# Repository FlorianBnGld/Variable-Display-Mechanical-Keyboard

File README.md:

### Florian Bonnet--Galand - ENSEA - 2025

# Le Clavier Reconfigurable

Ce projet s'inscrit dans l'option Maker de deuxième année à l'ENSEA. Il a été réalisé par Florian Bonnet--Galand.

---

#### Petite présentation vidéo du projet :

---

#### Le PCB

La première étape fut le design d'une PCB, intégrant les switchs Cherry MX RED, une STM32G474RET6, 4 multiplexeurs I2C TCA9548A, ainsi que des connecteurs 4 pins pour les écrans MCOT064032A1V-YI. Toutes les documentations et les fichiers du PCB sont à retrouver sur le GitHub du projet, juste en dessous. (Bon, vous êtes déjà dessus normalement mais bon...)

👉 [**Le GitHub du Projet**](https://github.com/FlorianBnGld/Variable-Display-Mechanical-Keyboard.git)

|  |  |
|:---:|:---:|

Ce premier design a été fait pour accueillir 30 touches, toutes similaires pour plus de modularité et accessoirement pour gagner du temps.

|  |
|:---:|

---

#### Les Keycaps

Un autre axe de travail sur lequel il a fallu plancher est celui des Keycaps.  
Il ne suffisait pas d'en trouver des correspondants sur Internet, mais bien de les faire sur mesure afin de les adapter aux écrans et aux switchs.  
Ils ont été imprimés en PLA sur des imprimantes Bambu Lab.

|  |  |
|:---:|:---:|

|  |  |
|:---:|:---:|

Ces Keycaps présentent un espace libre pour y placer l'écran, ainsi qu'une ouverture vers le dessous pour faire passer la nappe de connexion.

Au final, le modèle est assez satisfaisant :  
Ils s'adaptent parfaitement, aussi bien à la taille des écrans qui passent bien et surtout aux switchs.  
Les caps ne se retirent pas si facilement, bien que le modèle soit assez variable en fonction de la qualité d'impression.  
De plus, l'enlèvement du support était assez fastidieux et complexe sans endommager les keycaps.

|  | .jpg?raw=true) |
|:---:|:---:|

---

#### Ce qu'il reste à faire et potentielles améliorations futures

Afin de proposer un réel produit fini :
- Développer une interface utilisateur sur PC pour modifier ce que les touches tapent et ce qui s'affiche sur les écrans. (Actuellement géré par CubeIDE)
- Faire une V2 du PCB avec une alimentation plus viable (par exemple, un port USB au lieu d'un simple port JST).
- Commander des écrans similaires à celui des tests réussis (difficile à obtenir hors AliExpress).
- Créer une box imprimée en 3D ou découpée au laser pour accueillir le PCB (ce qui dépend de nombreux paramètres et n'a pas été réalisé par manque de temps).

---

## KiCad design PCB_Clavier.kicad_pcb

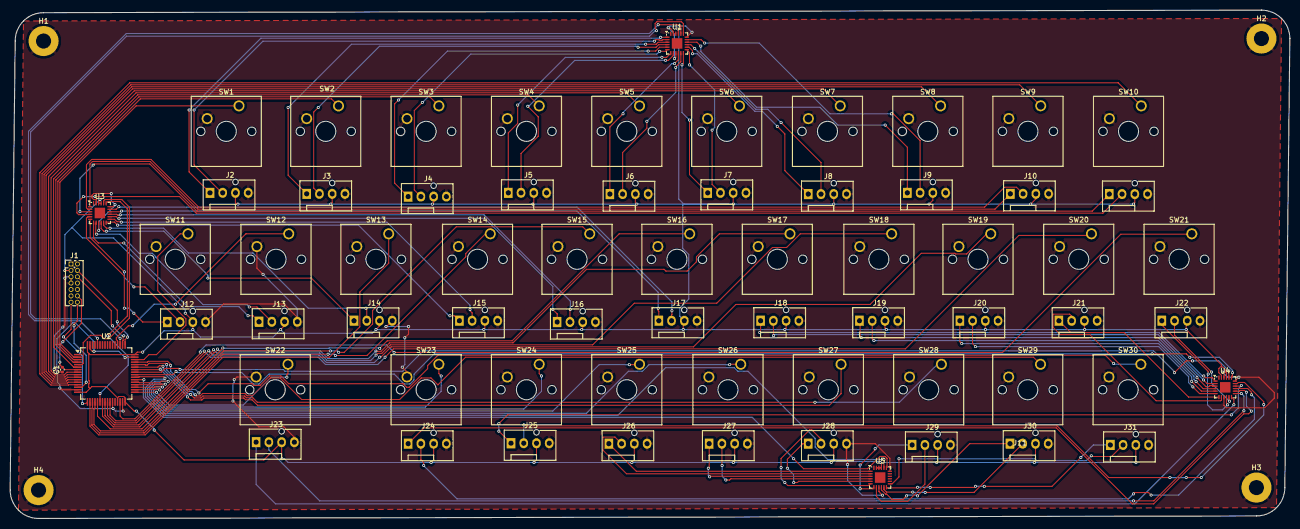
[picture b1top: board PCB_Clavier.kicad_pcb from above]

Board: 2 copper layers, 255.1 x 101.3 mm, 71 parts (0 on the bottom side), 105 nets.

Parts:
C1: 100n; C_0402_1005Metric
H1, H2, H3, H4: MountingHole_Pad; MountingHole_3mm_Pad
J1: Conn_ST_STDC14; PinHeader_2x07_P1.27mm_Vertical
J2, J3, J4, J5, J6, J7, J8, J9, J10, J11, J12, J13, J14, J15, J16, J17, J18, J19, J20, J21, J22, J23, J24, J25, J26, J27, J28, J29, J30, J31: Conn_01x04; FanPinHeader_1x04_P2.54mm_Vertical
SW1, SW2, SW3, SW4, SW5, SW6, SW7, SW8, SW9, SW10, SW11, SW12, SW13, SW14, SW15, SW16, SW17, SW18, SW19, SW20, SW21, SW22, SW23, SW24, SW25, SW26, SW27, SW28, SW29, SW30: CherryMX; SW_Cherry_MX_1.00u_PCB
U1, U3, U4, U5: TCA9548AMRGER; Texas_RGE0024C_VQFN-24-1EP_4x4mm_P0.5mm_EP2.1x2.1mm
U2: STM32G474RETx; LQFP-64_10x10mm_P0.5mm

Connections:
GND: C1.1, H1.1, H2.1, H3.1, H4.1, J1.5 (GND), J1.7 (GND), J2.4, J3.4, J4.4, J5.4, J6.4, J7.4, J8.4, J9.4, J10.4, J11.4, J12.4, J13.4, J14.4, J15.4, J16.4, J17.4, J18.4, J19.4, J20.4, J21.4, J22.4, J23.4, J24.4, J25.4, J26.4, J27.4, J28.4, J29.4, J30.4, J31.4, SW1.2, SW2.2, SW3.2, SW4.2, SW5.2, SW6.2, SW7.2, SW8.2, SW9.2, SW10.2, SW11.2, SW12.2, SW13.2, SW14.2, SW15.2, SW16.2, SW17.2, SW18.2, SW19.2, SW20.2, SW21.2, SW22.2, SW23.2, SW24.2, SW25.2, SW26.2, SW27.2, SW28.2, SW29.2, SW30.2, U1.9 (GND), U1.18 (A2), U1.22 (A0), U1.23 (A1), U2.15 (VSS), U2.27 (VSSA), U2.31 (VSS), U2.47 (VSS), U2.63 (VSS), U3.9 (GND), U3.18 (A2), U3.23 (A1), U4.9 (GND), U4.18 (A2), U4.22 (A0), U5.9 (GND), U5.18 (A2)
I2C1_SCL: U1.19 (SCL), U2.51 (PA15)
I2C1_SDA: U1.20 (SDA), U2.60 (PB7)
I2C2_SCL: U2.22 (PC4), U3.19 (SCL)
I2C2_SDA: U2.5 (PF0), U3.20 (SDA)
I2C3_SCL: U2.40 (PC8), U4.19 (SCL)
I2C3_SDA: U2.41 (PC9), U4.20 (SDA)
I2C4_SCL: U2.38 (PC6), U5.19 (SCL)
I2C4_SDA: U2.39 (PC7), U5.20 (SDA)
NRST: C1.2, J1.12 (~RST), U2.7 (PG10)
SC1: J2.2, U1.2 (SC0)
SC2: J3.2, U1.4 (SC1)
SC3: J4.2, U1.6 (SC2)
SC4: J5.2, U1.8 (SC3)
SC5: J6.2, U1.11 (SC4)
SC6: J7.2, U1.13 (SC5)
SC7: J8.2, U1.15 (SC6)
SC8: J9.2, U1.17 (SC7)
SC9: J10.2, U3.2 (SC0)
SC10: J11.2, U3.4 (SC1)
SC11: J12.2, U3.6 (SC2)
SC12: J13.2, U3.8 (SC3)
SC13: J14.2, U3.11 (SC4)
SC14: J15.2, U3.13 (SC5)
SC15: J16.2, U3.15 (SC6)
SC16: J17.2, U3.17 (SC7)
SC17: J18.2, U4.2 (SC0)
SC18: J19.2, U4.4 (SC1)
SC19: J20.2, U4.6 (SC2)
SC20: J21.2, U4.8 (SC3)
SC21: J22.2, U4.11 (SC4)
SC22: J23.2, U4.13 (SC5)
SC23: J24.2, U4.15 (SC6)
SC24: J25.2, U4.17 (SC7)
SC25: J26.2, U5.2 (SC0)
SC26: J27.2, U5.4 (SC1)
SC27: J28.2, U5.6 (SC2)
SC28: J29.2, U5.8 (SC3)
SC29: J30.2, U5.11 (SC4)
SC30: J31.2, U5.13 (SC5)
SD1: J2.1, U1.1 (SD0)
SD2: J3.1, U1.3 (SD1)
SD3: J4.1, U1.5 (SD2)
SD4: J5.1, U1.7 (SD3)
SD5: J6.1, U1.10 (SD4)
SD6: J7.1, U1.12 (SD5)
SD7: J8.1, U1.14 (SD6)
SD8: J9.1, U1.16 (SD7)
SD9: J10.1, U3.1 (SD0)
SD10: J11.1, U3.3 (SD1)
SD11: J12.1, U3.5 (SD2)
SD12: J13.1, U3.7 (SD3)
SD13: J14.1, U3.10 (SD4)
SD14: J15.1, U3.12 (SD5)
SD15: J16.1, U3.14 (SD6)
SD16: J17.1, U3.16 (SD7)
SD17: J18.1, U4.1 (SD0)
SD18: J19.1, U4.3 (SD1)
SD19: J20.1, U4.5 (SD2)
SD20: J21.1, U4.7 (SD3)
SD21: J22.1, U4.10 (SD4)
SD22: J23.1, U4.12 (SD5)
SD23: J24.1, U4.14 (SD6)
SD24: J25.1, U4.16 (SD7)
SD25: J26.1, U5.1 (SD0)
SD26: J27.1, U5.3 (SD1)
SD27: J28.1, U5.5 (SD2)
SD28: J29.1, U5.7 (SD3)
SD29: J30.1, U5.10 (SD4)
SD30: J31.1, U5.12 (SD5)
SWCLK: J1.6 (JCLK/SWCLK), U2.50 (PA14)
SWDIO: J1.4 (JTMS/SWDIO), U2.49 (PA13)
Switch1: SW1.1, U2.2 (PC13)
Switch2: SW2.1, U2.3 (PC14)
Switch3: SW3.1, U2.4 (PC15)
Switch4: SW4.1, U2.6 (PF1)
Switch5: SW5.1, U2.8 (PC0)
Switch6: SW6.1, U2.9 (PC1)
Switch7: SW7.1, U2.10 (PC2)
Switch8: SW8.1, U2.11 (PC3)
Switch9: SW9.1, U2.12 (PA0)
Switch10: SW10.1, U2.13 (PA1)
Switch11: SW11.1, U2.46 (PA12)
Switch12: SW12.1, U2.52 (PC10)
Switch13: SW13.1, U2.18 (PA4)
Switch14: SW14.1, U2.19 (PA5)
Switch15: SW15.1, U2.20 (PA6)
Switch16: SW16.1, U2.21 (PA7)
Switch17: SW17.1, U2.23 (PC5)
Switch18: SW18.1, U2.24 (PB0)
Switch19: SW19.1, U2.25 (PB1)
Switch20: SW20.1, U2.26 (PB2)
Switch21: SW21.1, U2.30 (PB10)
Switch22: SW22.1, U2.33 (PB11)
Switch23: SW23.1, U2.34 (PB12)
Switch24: SW24.1, U2.35 (PB13)
Switch25: SW25.1, U2.36 (PB14)
Switch26: SW26.1, U2.37 (PB15)
Switch27: SW27.1, U2.42 (PA8)
Switch28: SW28.1, U2.43 (PA9)
Switch29: SW29.1, U2.44 (PA10)
Switch30: SW30.1, U2.45 (PA11)
USART2_RX: J1.13 (VCP_RX), U2.17 (PA3)
USART2_TX: J1.14 (VCP_TX), U2.14 (PA2)
VCC: J1.3 (VCC), J2.3, J3.3, J4.3, J5.3, J6.3, J7.3, J8.3, J9.3, J10.3, J11.3, J12.3, J13.3, J14.3, J15.3, J16.3, J17.3, J18.3, J19.3, J20.3, J21.3, J22.3, J23.3, J24.3, J25.3, J26.3, J27.3, J28.3, J29.3, J30.3, J31.3, U1.21 (VCC), U2.16 (VDD), U2.29 (VDDA), U2.32 (VDD), U2.48 (VDD), U2.64 (VDD), U3.21 (VCC), U3.22 (A0), U4.21 (VCC), U4.23 (A1), U5.21 (VCC), U5.22 (A0), U5.23 (A1)

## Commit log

2025-03-24 Create PCB_Clavier
2025-04-24 Create kicad
2025-04-24 Create model
2025-04-26 Create test
2025-04-27 Create datasheets
2025-04-27 Create écrans
